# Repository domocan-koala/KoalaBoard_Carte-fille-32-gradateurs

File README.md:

# Carte fille 32 gradateurs version 1.0

Carte fille 32 gradateurs compatible KoalaBoard pour le système domotique [Domocan](https://www.abcelectronique.com/bigonoff/forum/index.php)

## Historique
	
	* 23/02/18 V1.0 : Première version mise en ligne

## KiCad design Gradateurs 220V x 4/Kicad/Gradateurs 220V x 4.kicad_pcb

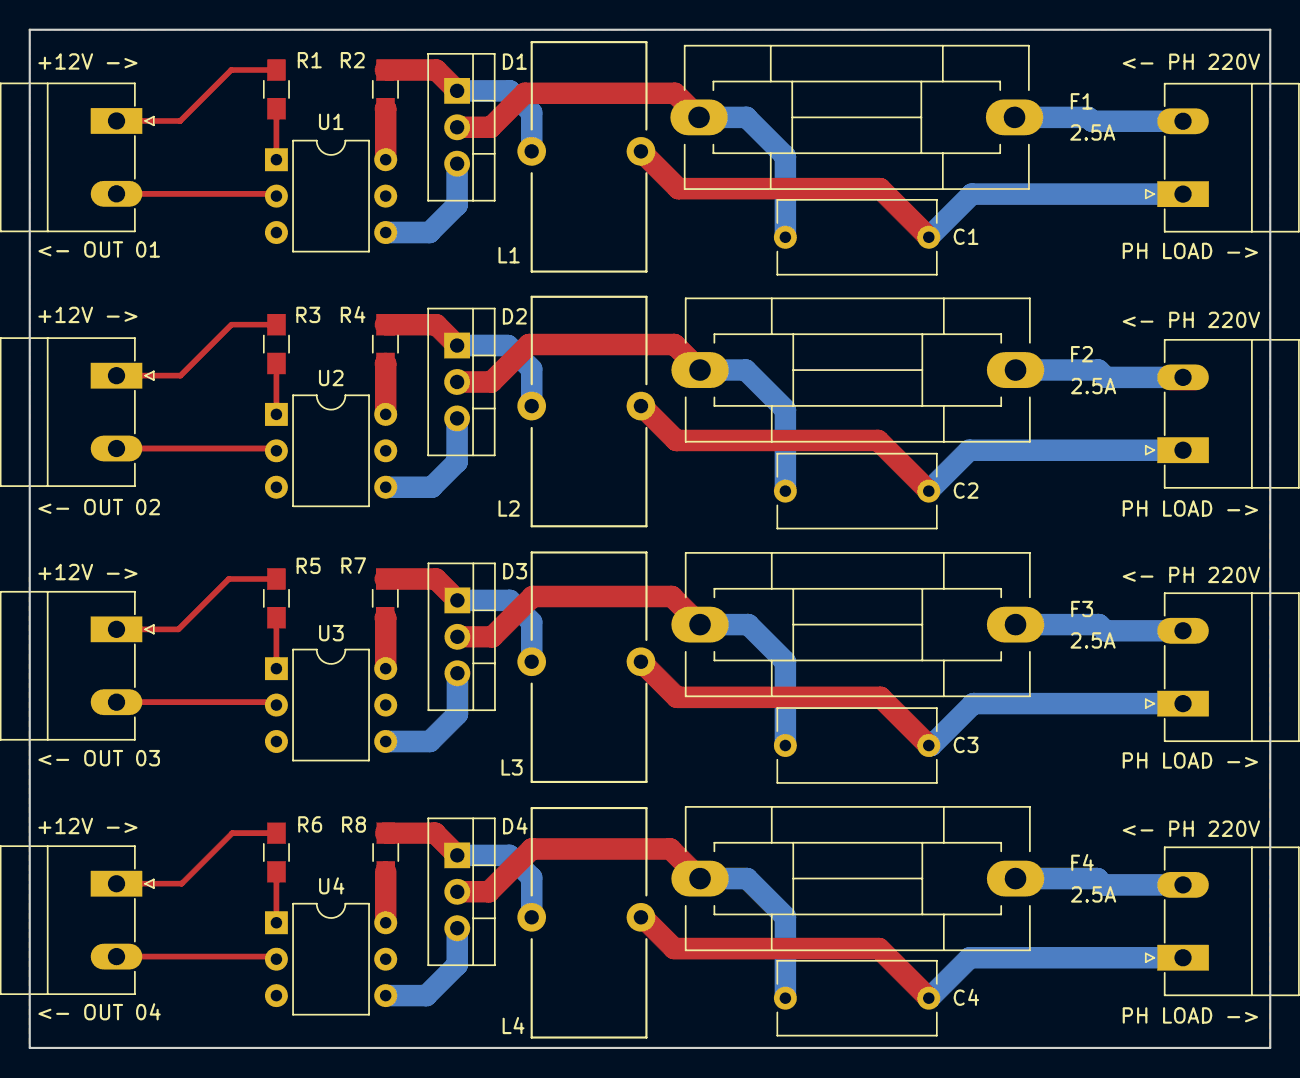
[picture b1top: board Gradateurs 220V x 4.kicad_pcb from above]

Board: 2 copper layers, 86.5 x 71.0 mm, 37 parts (1 on the bottom side), 36 nets.

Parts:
C1, C2, C3, C4: 47nF/630V X2; C_Rect_L11.0mm_W5.1mm_P10.00mm_MKT
D1, D2, D3, D4: BT139; TO-220-3_Vertical
F1, F2, F3, F4: 2.5A; Fuseholder5x20_horiz_SemiClosed_Casing10x25mm
J1, J3, J5, J6: MCU; PhoenixContact_MC-G_02x5.08mm_Angled
J2, J4, J7, J8: 220V; PhoenixContact_MC-G_02x5.08mm_Angled
L1, L2, L3, L4: 47uH; Choke_Toroid_8x16mm_Vertical
LG1: Koala; koala
R1, R3, R5, R6: 470R; R_0805_HandSoldering
R2, R4, R7, R8: 4K7; R_0805_HandSoldering
U1, U2, U3, U4: MOC2030; DIP-6_W7.62mm

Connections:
unnamed: C1.1, J2.1, L1.2
unnamed: C1.2, D1.2, F1.2
unnamed: C2.1, J4.1, L2.2
unnamed: C2.2, D2.2, F2.2
unnamed: C3.1, J7.1, L3.2
unnamed: C3.2, D3.2, F3.2
unnamed: C4.1, J8.1, L4.2
unnamed: C4.2, D4.2, F4.2
unnamed: D1.1, L1.1, R2.1
unnamed: D1.3, U1.4
unnamed: D2.1, L2.1, R4.1
unnamed: D2.3, U2.4
unnamed: D3.1, L3.1, R7.1
unnamed: D3.3, U3.4
unnamed: D4.1, L4.1, R8.1
unnamed: D4.3, U4.4
unnamed: F1.1, J2.2
unnamed: F2.1, J4.2
unnamed: F3.1, J7.2
unnamed: F4.1, J8.2
unnamed: J1.1, R1.2
unnamed: J1.2, U1.2
unnamed: J3.1, R3.2
unnamed: J3.2, U2.2
unnamed: J5.1, R5.2
unnamed: J5.2, U3.2
unnamed: J6.1, R6.2
unnamed: J6.2, U4.2
unnamed: R1.1, U1.1
unnamed: R2.2, U1.6
unnamed: R3.1, U2.1
unnamed: R4.2, U2.6
unnamed: R5.1, U3.1
unnamed: R6.1, U4.1
unnamed: R7.2, U3.6
unnamed: R8.2, U4.6

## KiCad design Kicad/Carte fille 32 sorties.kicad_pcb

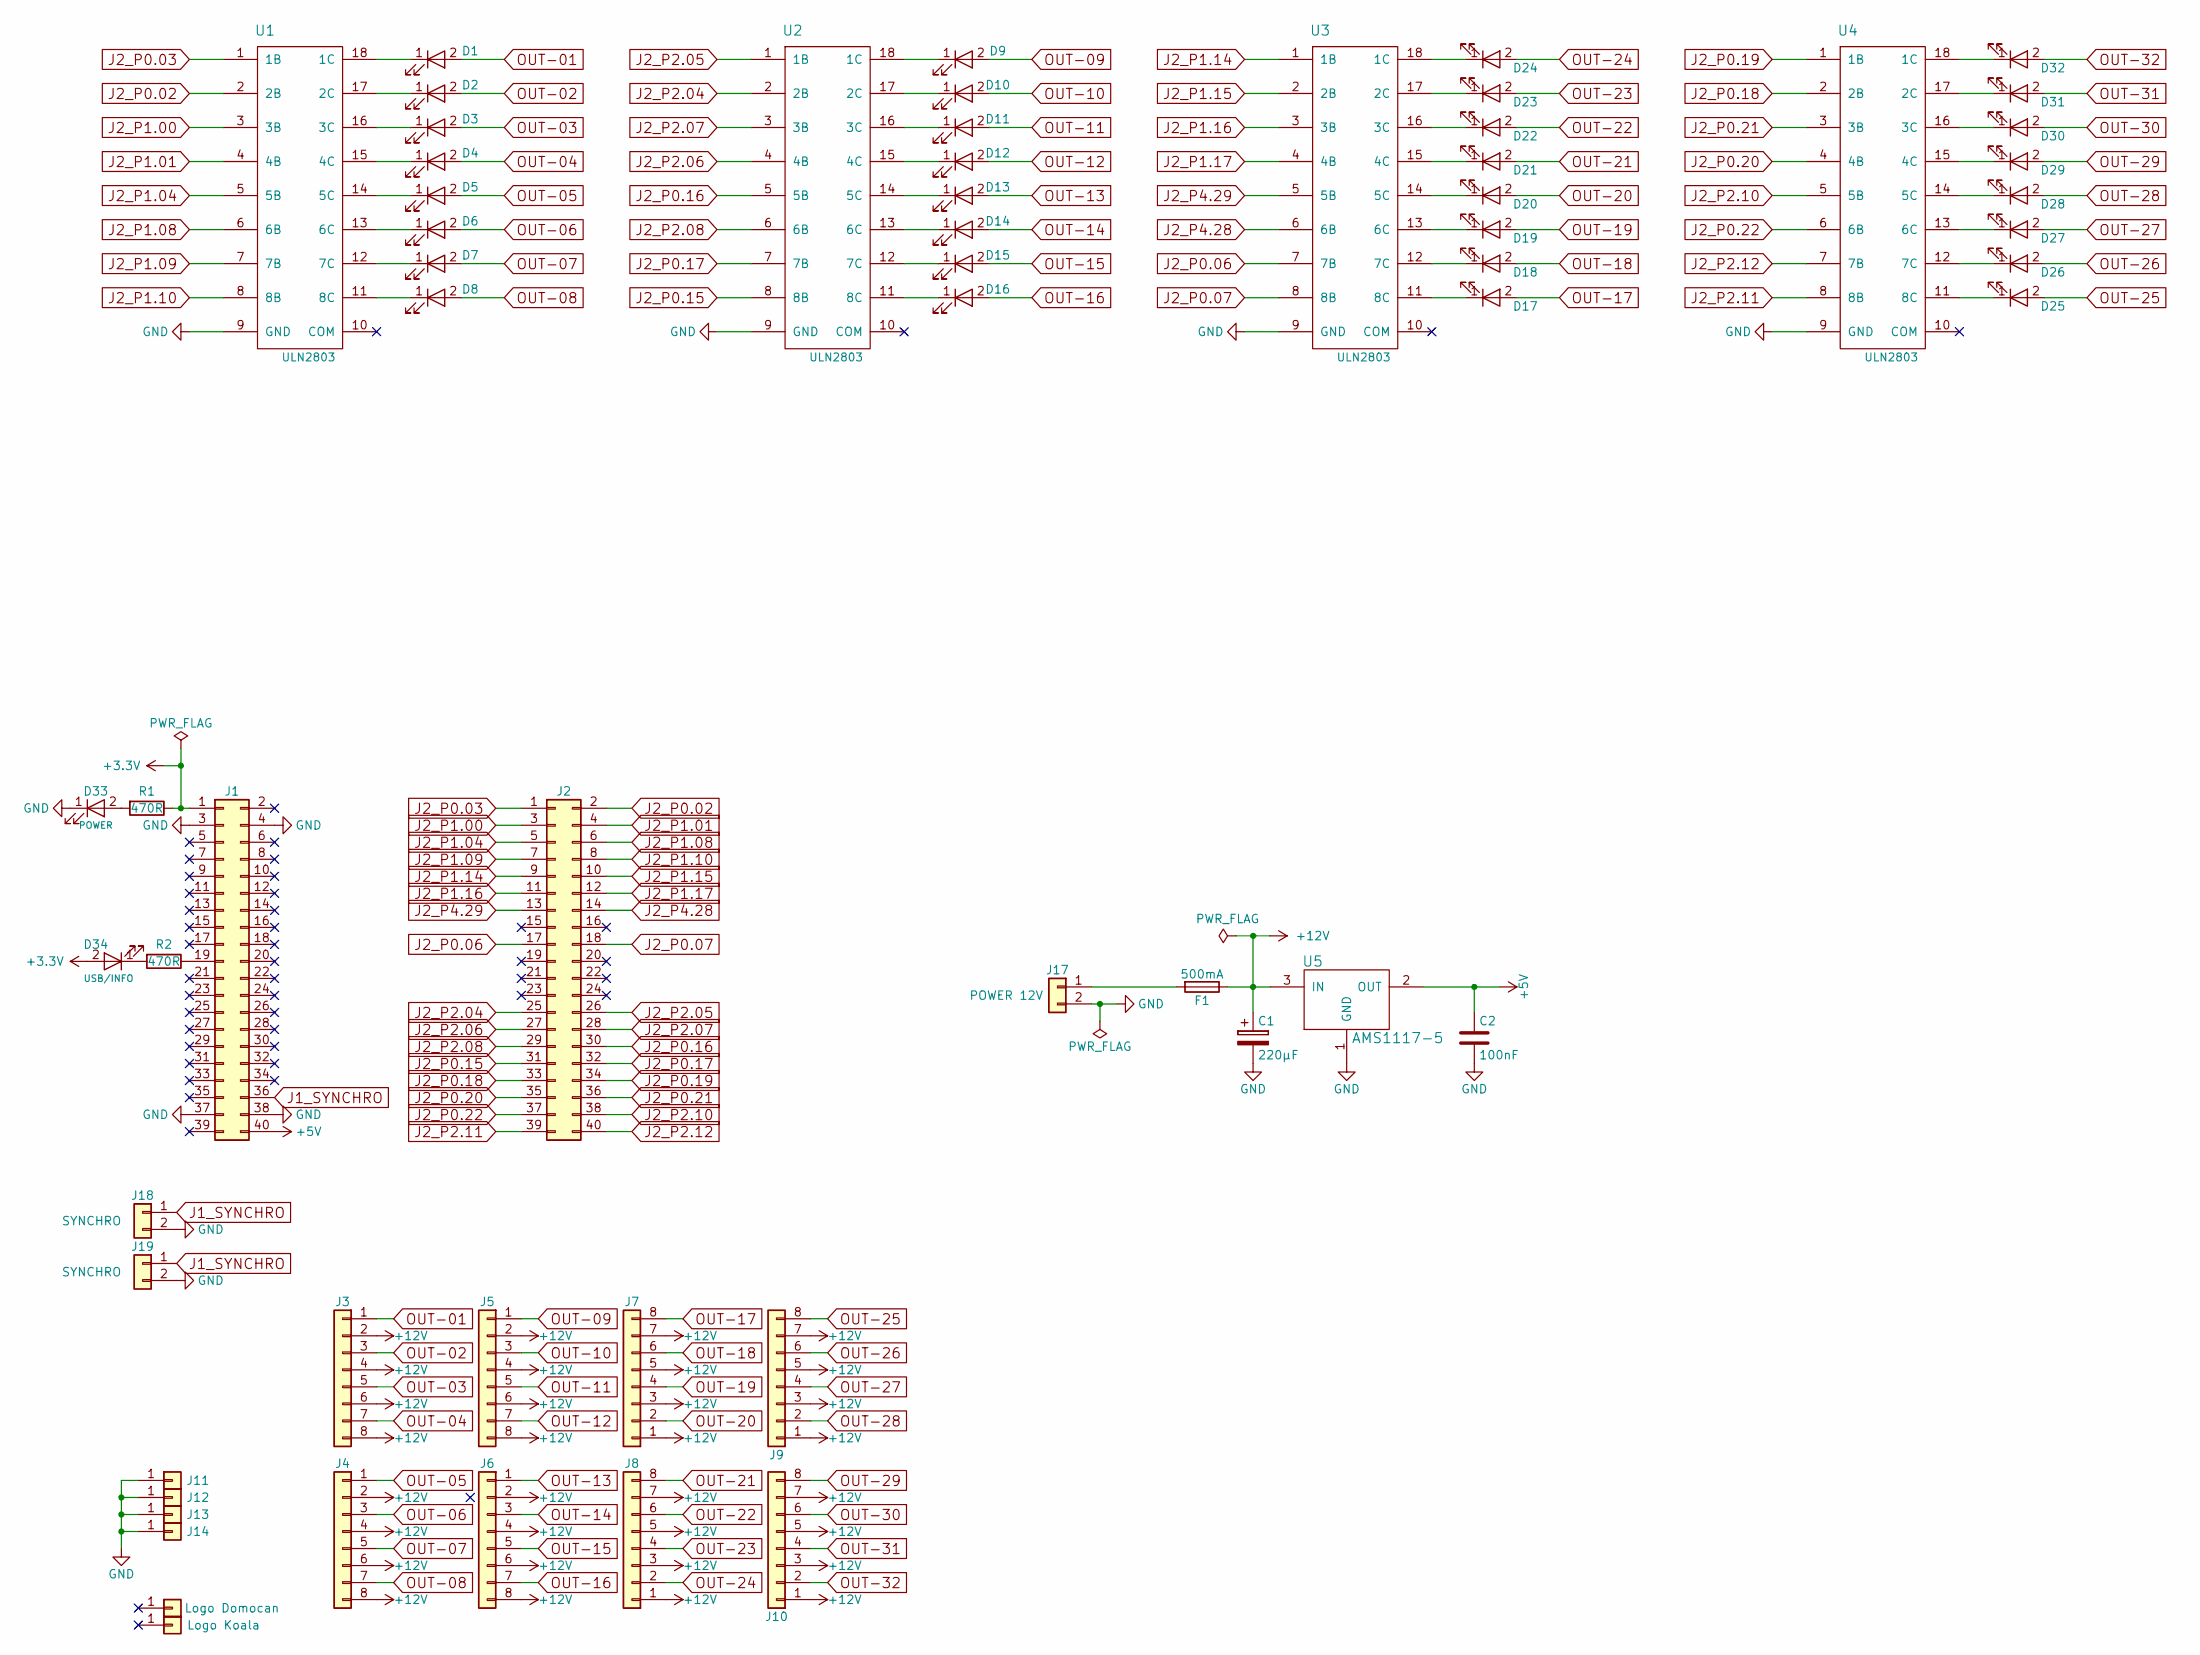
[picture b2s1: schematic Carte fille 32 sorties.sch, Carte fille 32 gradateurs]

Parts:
C1: 220µF; CP_Elec_6.3x7.7
C2: 100nF; C_0805_HandSoldering
D1, D2, D3, D4, D5, D6, D7, D8, D9, D10, D11, D12, D13, D14, D15, D16, D17, D18, D19, D20, D21, D22, D23, D24, D25, D26, D27, D28, D29, D30, D31, D32: LED; LED_0805_HandSoldering
D33: POWER; LED_0805_HandSoldering
D34: USB/INFO; LED_0805_HandSoldering
F1: 500mA; Fuse_SMD1206_HandSoldering
J1, J2: Conn_02x20_Odd_Even; Socket_Strip_Straight_2x20_Pitch2.54mm
J3, J4, J5, J6, J7, J8, J9, J10: Conn_01x08; Pin_Header_Angled_1x08
J11, J12, J13, J14: Conn_01x01; MountingHole_3.5mm_Pad
J15: Logo Domocan; usb
J16: Logo Koala; koala
J17: POWER 12V; Pin_Header_Angled_1x02
J18, J19: SYNCHRO; Pin_Header_Angled_1x02
R1, R2: 470R; R_0805_HandSoldering
U1, U2, U3, U4: ULN2803; DIP-18_W7.62mm
U5: AMS1117-5; SOT-223

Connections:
+3V3: D34.2 (A), J1.1, R1.1
+5V: C2.1, J1.40, U5.2 (OUT)
+12V: C1.1, F1.1, J3.2, J3.4, J3.6, J3.8, J4.2, J4.4, J4.6, J4.8, J5.2, J5.4, J5.6, J5.8, J6.2, J6.4, J6.6, J6.8, J7.1, J7.3, J7.5, J7.7, J8.1, J8.3, J8.5, J8.7, J9.1, J9.3, J9.5, J9.7, J10.1, J10.3, J10.5, J10.7, U5.3 (IN)
GND: C1.2, C2.2, D33.1 (K), J1.3, J1.4, J1.37, J1.38, J11.1, J12.1, J13.1, J14.1, J17.2, J18.2, J19.2, U1.9 (GND), U2.9 (GND), U3.9 (GND), U4.9 (GND), U5.1 (GND)
J2_P0.02: J2.2, U1.2 (2B)
J2_P0.03: J2.1, U1.1 (1B)
J2_P0.06: J2.17, U3.7 (7B)
J2_P0.07: J2.18, U3.8 (8B)
J2_P0.15: J2.31, U2.8 (8B)
J2_P0.16: J2.30, U2.5 (5B)
J2_P0.17: J2.32, U2.7 (7B)
J2_P0.18: J2.33, U4.2 (2B)
J2_P0.19: J2.34, U4.1 (1B)
J2_P0.20: J2.35, U4.4 (4B)
J2_P0.21: J2.36, U4.3 (3B)
J2_P0.22: J2.37, U4.6 (6B)
J2_P1.00: J2.3, U1.3 (3B)
J2_P1.01: J2.4, U1.4 (4B)
J2_P1.04: J2.5, U1.5 (5B)
J2_P1.08: J2.6, U1.6 (6B)
J2_P1.09: J2.7, U1.7 (7B)
J2_P1.10: J2.8, U1.8 (8B)
J2_P1.14: J2.9, U3.1 (1B)
J2_P1.15: J2.10, U3.2 (2B)
J2_P1.16: J2.11, U3.3 (3B)
J2_P1.17: J2.12, U3.4 (4B)
J2_P2.04: J2.25, U2.2 (2B)
J2_P2.05: J2.26, U2.1 (1B)
J2_P2.06: J2.27, U2.4 (4B)
J2_P2.07: J2.28, U2.3 (3B)
J2_P2.08: J2.29, U2.6 (6B)
J2_P2.10: J2.38, U4.5 (5B)
J2_P2.11: J2.39, U4.8 (8B)
J2_P2.12: J2.40, U4.7 (7B)
J2_P4.28: J2.14, U3.6 (6B)
J2_P4.29: J2.13, U3.5 (5B)
unnamed: D1.1 (K), U1.18 (1C)
unnamed: D2.1 (K), U1.17 (2C)
unnamed: D3.1 (K), U1.16 (3C)
unnamed: D4.1 (K), U1.15 (4C)
unnamed: D5.1 (K), U1.14 (5C)
unnamed: D6.1 (K), U1.13 (6C)
unnamed: D7.1 (K), U1.12 (7C)
unnamed: D8.1 (K), U1.11 (8C)
unnamed: D9.1 (K), U2.18 (1C)
unnamed: D10.1 (K), U2.17 (2C)
unnamed: D11.1 (K), U2.16 (3C)
unnamed: D12.1 (K), U2.15 (4C)
unnamed: D13.1 (K), U2.14 (5C)
unnamed: D14.1 (K), U2.13 (6C)
unnamed: D15.1 (K), U2.12 (7C)
unnamed: D16.1 (K), U2.11 (8C)
unnamed: D17.1 (K), U3.11 (8C)
unnamed: D18.1 (K), U3.12 (7C)
unnamed: D19.1 (K), U3.13 (6C)
unnamed: D20.1 (K), U3.14 (5C)
unnamed: D21.1 (K), U3.15 (4C)
unnamed: D22.1 (K), U3.16 (3C)
unnamed: D23.1 (K), U3.17 (2C)
unnamed: D24.1 (K), U3.18 (1C)
unnamed: D25.1 (K), U4.11 (8C)
unnamed: D26.1 (K), U4.12 (7C)
unnamed: D27.1 (K), U4.13 (6C)
unnamed: D28.1 (K), U4.14 (5C)
unnamed: D29.1 (K), U4.15 (4C)
unnamed: D30.1 (K), U4.16 (3C)
unnamed: D31.1 (K), U4.17 (2C)
unnamed: D32.1 (K), U4.18 (1C)
unnamed: D33.2 (A), R1.2
unnamed: D34.1 (K), R2.2
unnamed: F1.2, J17.1
unnamed: J1.19, R2.1
OUT-01: D1.2 (A), J3.1
OUT-02: D2.2 (A), J3.3
OUT-03: D3.2 (A), J3.5
OUT-04: D4.2 (A), J3.7
OUT-05: D5.2 (A), J4.1
OUT-06: D6.2 (A), J4.3
OUT-07: D7.2 (A), J4.5
OUT-08: D8.2 (A), J4.7
OUT-09: D9.2 (A), J5.1
OUT-10: D10.2 (A), J5.3
OUT-11: D11.2 (A), J5.5
OUT-12: D12.2 (A), J5.7
OUT-13: D13.2 (A), J6.1
OUT-14: D14.2 (A), J6.3
OUT-15: D15.2 (A), J6.5
OUT-16: D16.2 (A), J6.7
OUT-17: D17.2 (A), J7.8
OUT-18: D18.2 (A), J7.6
OUT-19: D19.2 (A), J7.4
OUT-20: D20.2 (A), J7.2
OUT-21: D21.2 (A), J8.8
OUT-22: D22.2 (A), J8.6
OUT-23: D23.2 (A), J8.4
OUT-24: D24.2 (A), J8.2
OUT-25: D25.2 (A), J9.8
OUT-26: D26.2 (A), J9.6
OUT-27: D27.2 (A), J9.4
OUT-28: D28.2 (A), J9.2
OUT-29: D29.2 (A), J10.8
OUT-30: D30.2 (A), J10.6
OUT-31: D31.2 (A), J10.4
OUT-32: D32.2 (A), J10.2
SYNCHRO: J1.36, J18.1, J19.1

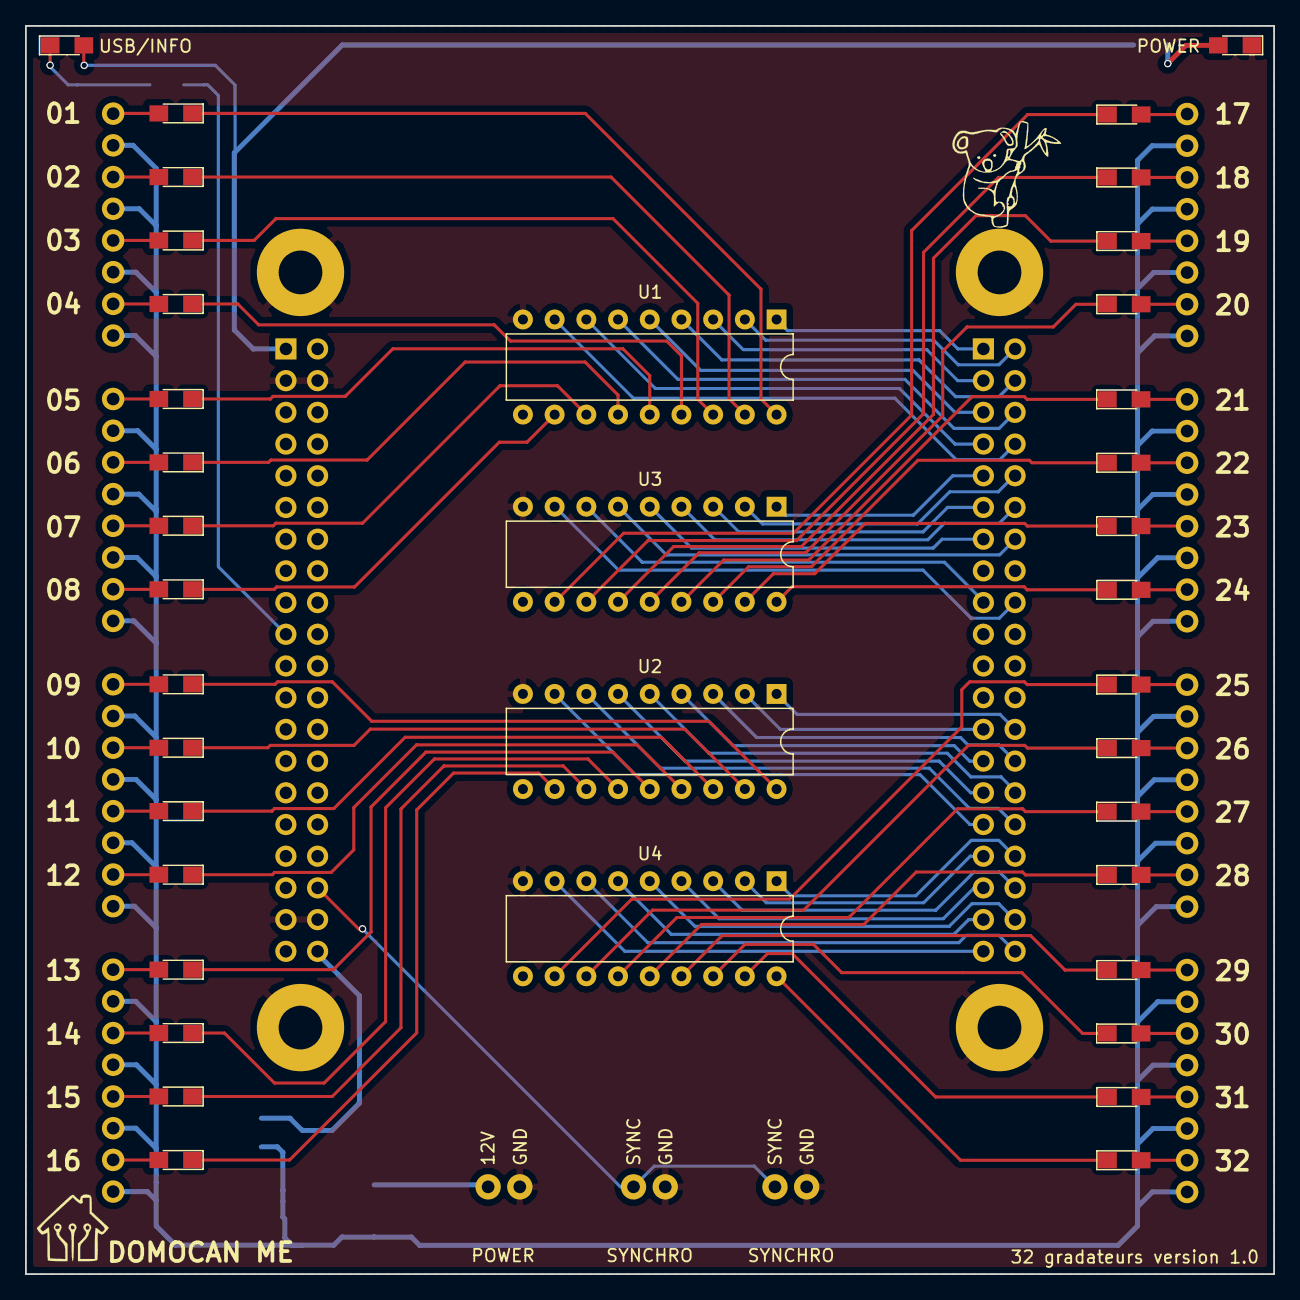
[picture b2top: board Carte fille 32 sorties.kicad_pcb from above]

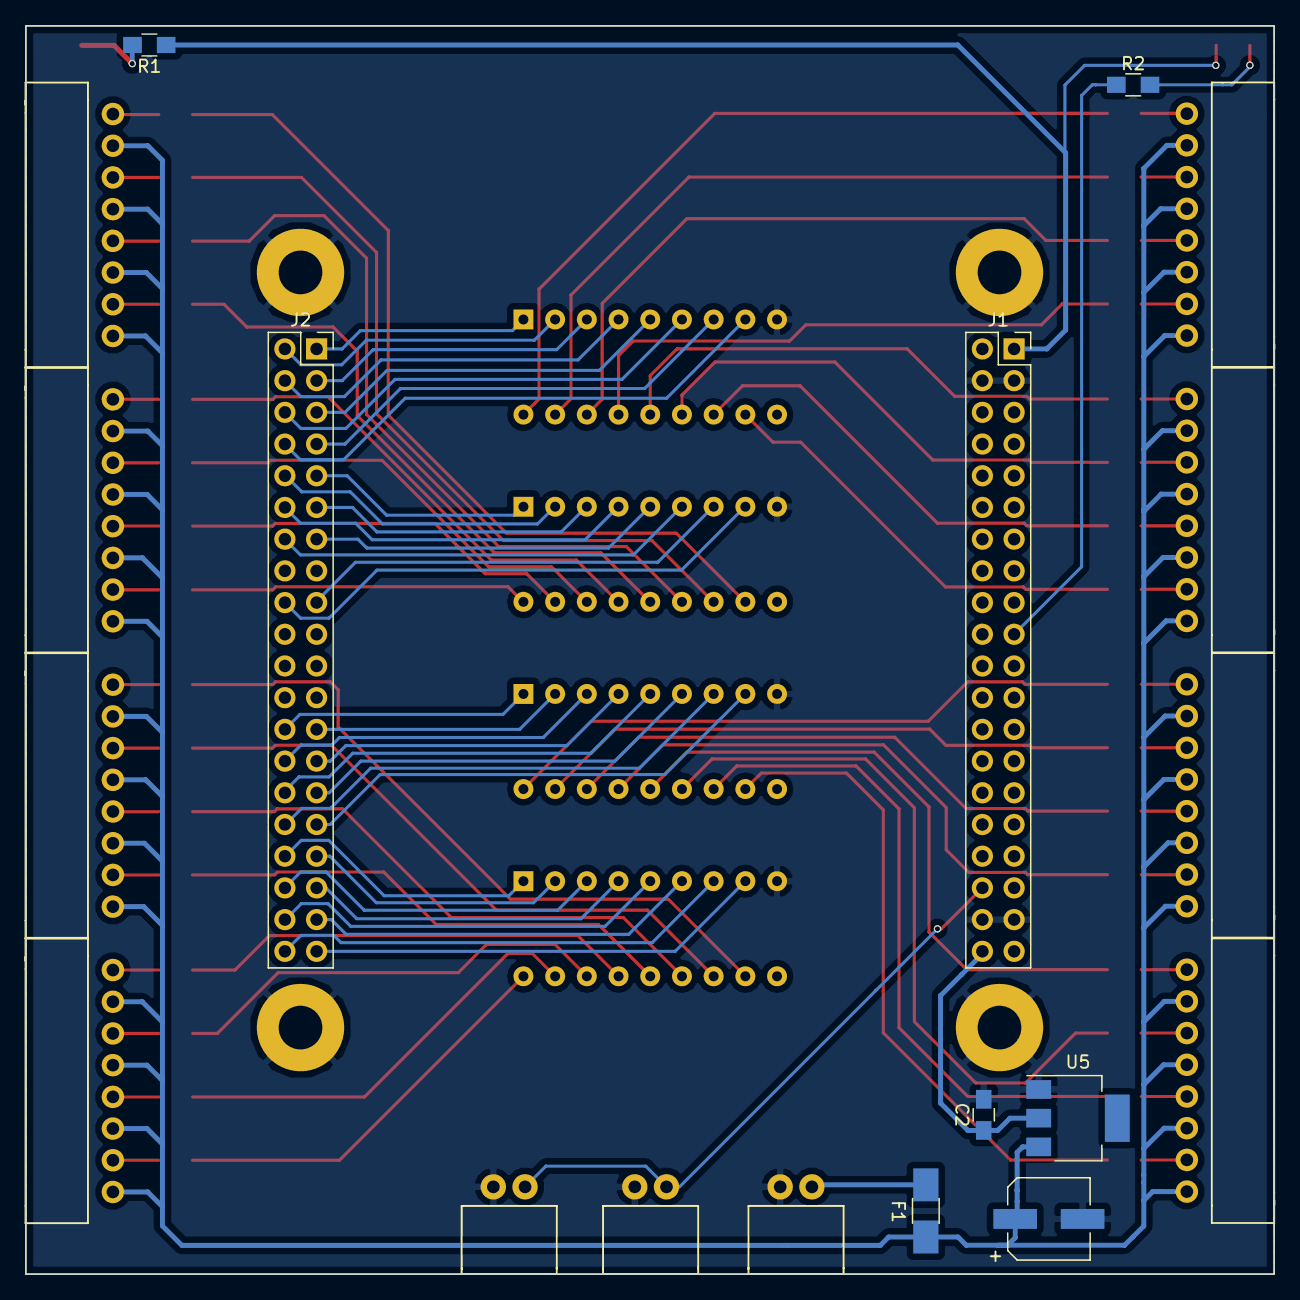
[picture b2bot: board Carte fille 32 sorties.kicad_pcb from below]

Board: 2 copper layers, 100.0 x 100.0 mm, 63 parts (19 on the bottom side), 105 nets.

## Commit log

2018-02-23 Première mise en ligne
    Carte fille 32 gradateurs compatible KoalaBoard pour le système
    domotique Domocan
2018-02-27 Correction vue 3D
2018-04-05 Ajout carte puissance 220V
2018-04-05 Correction sérigraphie
